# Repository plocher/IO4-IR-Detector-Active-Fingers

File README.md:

# IO4-IR-Detector-GBunza-Fingers
## License: CERN Open Hardware Licence v1.2

Active IR Detector subassemblies made to look like N or HO scale ties.

Works with SPCoast [IO4-IR-Detector-Active](/pages/IO4-IR-Detector-Active) IR Detector

  * Fab with a BLACK silk screen to help blend in to the trackwork.
  * Cut to length for N scale

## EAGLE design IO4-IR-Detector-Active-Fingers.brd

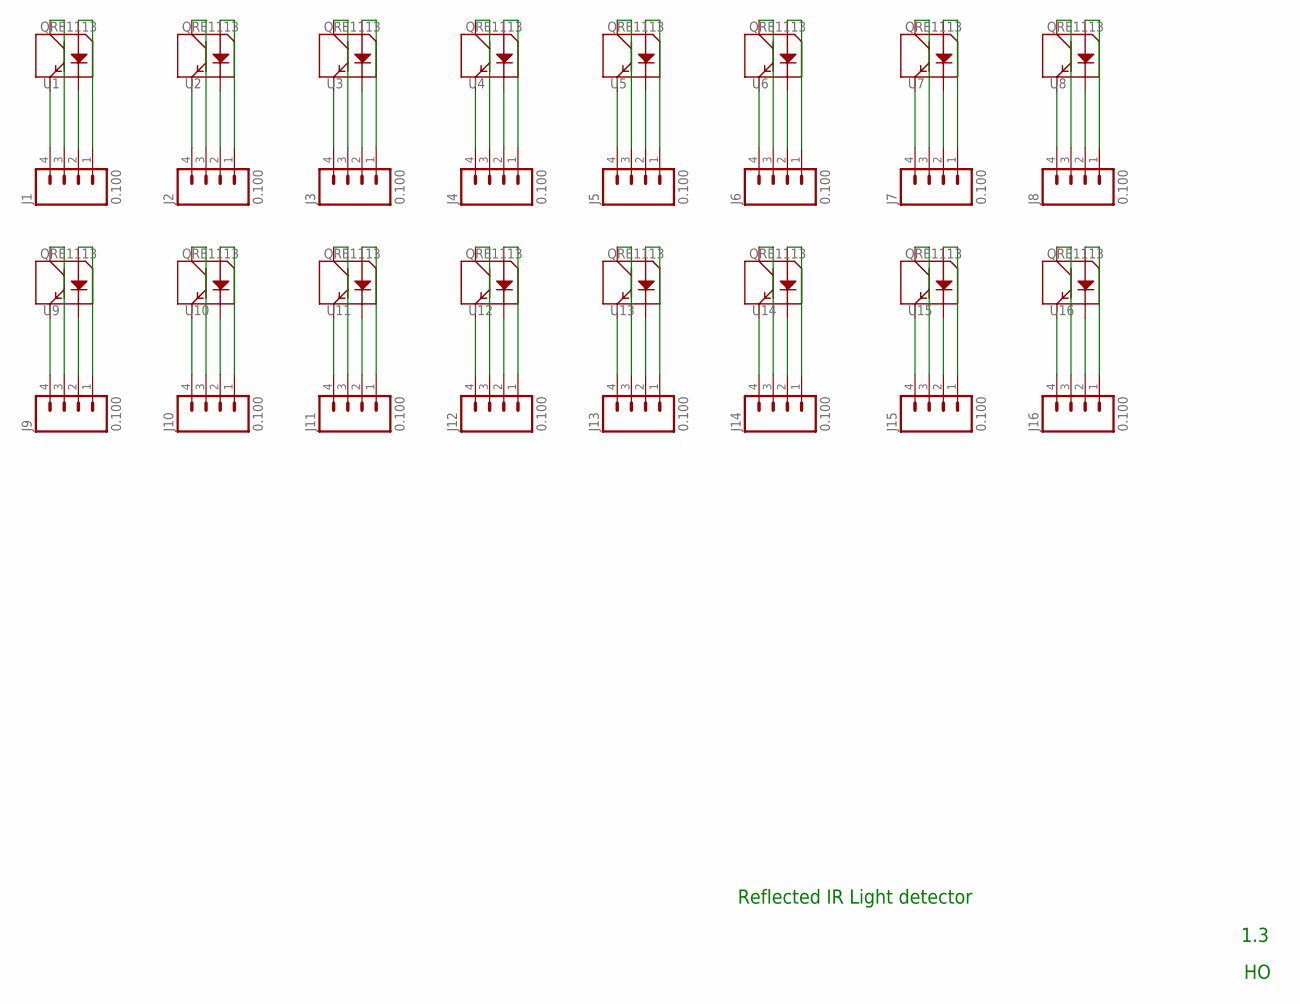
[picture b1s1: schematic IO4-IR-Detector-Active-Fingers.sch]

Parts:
J1, J2, J3, J4, J5, J6, J7, J8, J9, J10, J11, J12, J13, J14, J15, J16: 0.100; 1X04_LOCK
U1, U2, U3, U4, U5, U6, U7, U8, U9, U10, U11, U12, U13, U14, U15, U16: QRE1113

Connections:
unnamed: J1.4, U1.4 (E)
unnamed: J1.2, U1.2 (K)
unnamed: J1.1, U1.1 (A)
unnamed: J4.4, U4.4 (E)
unnamed: J4.2, U4.2 (K)
unnamed: J4.1, U4.1 (A)
unnamed: J1.3, U1.3 (C)
unnamed: J6.1, U6.1 (A)
unnamed: J7.1, U7.1 (A)
unnamed: J8.1, U8.1 (A)
unnamed: J9.1, U9.1 (A)
unnamed: J10.1, U10.1 (A)
unnamed: J11.1, U11.1 (A)
unnamed: J12.1, U12.1 (A)
unnamed: J13.1, U13.1 (A)
unnamed: J14.1, U14.1 (A)
unnamed: J15.1, U15.1 (A)
unnamed: J16.1, U16.1 (A)
unnamed: J2.4, U2.4 (E)
unnamed: J2.2, U2.2 (K)
unnamed: J2.1, U2.1 (A)
unnamed: J3.4, U3.4 (E)
unnamed: J3.2, U3.2 (K)
unnamed: J3.1, U3.1 (A)
unnamed: J2.3, U2.3 (C)
unnamed: J5.4, U5.4 (E)
unnamed: J5.2, U5.2 (K)
unnamed: J5.1, U5.1 (A)
unnamed: J6.4, U6.4 (E)
unnamed: J6.2, U6.2 (K)
unnamed: J3.3, U3.3 (C)
unnamed: J7.4, U7.4 (E)
unnamed: J7.2, U7.2 (K)
unnamed: J4.3, U4.3 (C)
unnamed: J8.4, U8.4 (E)
unnamed: J8.2, U8.2 (K)
unnamed: J5.3, U5.3 (C)
unnamed: J9.4, U9.4 (E)
unnamed: J9.2, U9.2 (K)
unnamed: J7.3, U7.3 (C)
unnamed: J8.3, U8.3 (C)
unnamed: J16.3, U16.3 (C)
unnamed: J15.3, U15.3 (C)
unnamed: J14.3, U14.3 (C)
unnamed: J10.4, U10.4 (E)
unnamed: J10.2, U10.2 (K)
unnamed: J13.3, U13.3 (C)
unnamed: J11.4, U11.4 (E)
unnamed: J11.2, U11.2 (K)
unnamed: J12.3, U12.3 (C)
unnamed: J12.4, U12.4 (E)
unnamed: J12.2, U12.2 (K)
unnamed: J13.4, U13.4 (E)
unnamed: J13.2, U13.2 (K)
unnamed: J11.3, U11.3 (C)
unnamed: J14.4, U14.4 (E)
unnamed: J14.2, U14.2 (K)
unnamed: J15.4, U15.4 (E)
unnamed: J15.2, U15.2 (K)
unnamed: J16.4, U16.4 (E)
unnamed: J16.2, U16.2 (K)
unnamed: J10.3, U10.3 (C)
unnamed: J9.3, U9.3 (C)
unnamed: J6.3, U6.3 (C)

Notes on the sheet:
Reflected IR Light detector
1.3

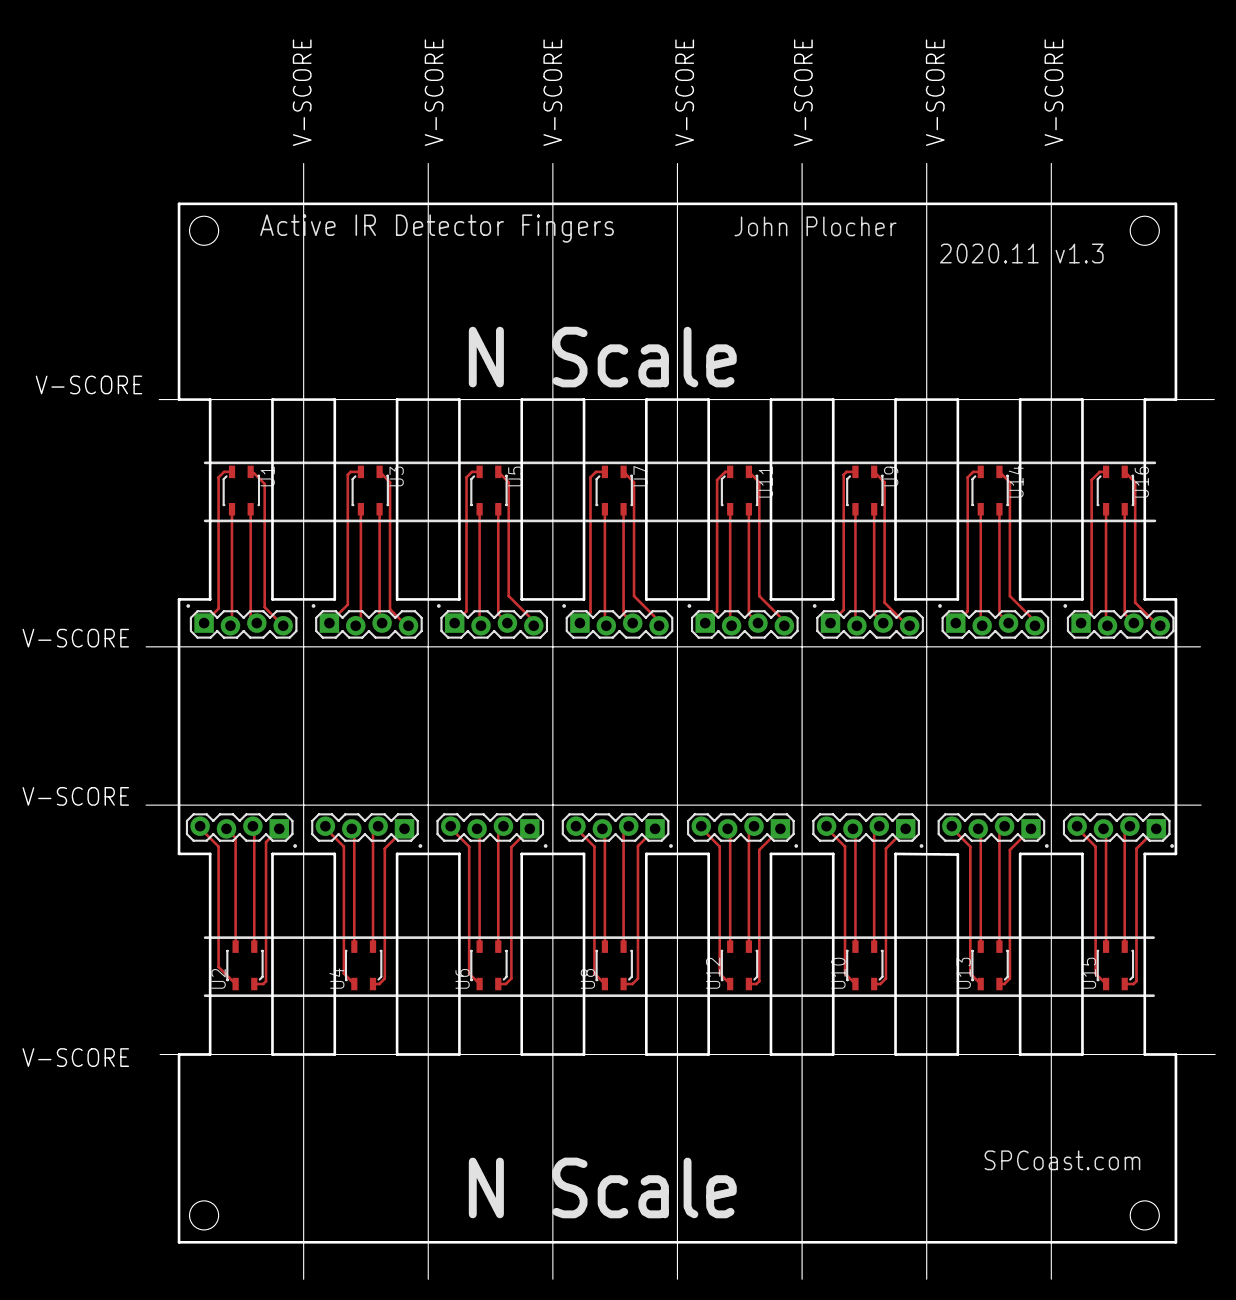
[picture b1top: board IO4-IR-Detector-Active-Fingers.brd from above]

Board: 2 copper layers, 103.0 x 107.4 mm, 32 parts (0 on the bottom side), 64 nets.

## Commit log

2020-11-28 Initial version
2020-11-30 JLC requires 6mm board width, switch to QRE1113GR
2020-12-12 HO FatFingers
2020-12-12 silk
2020-12-12 N-Scale
